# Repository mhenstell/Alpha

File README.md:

Alpha
======

Alpha is an Arduino-compatible display that includes five ultra-bright 18-segment alphanumeric displays. It's powered by USB or external supply, and can be daisy-chained. It's also internet-enabled with the inclusion of a Wifi-enabled Spark Core.

I was inspired to build the Alpha by Windell Oskay's [Alpha Clock Five](http://shop.evilmadscientist.com/productsmenu/tinykitlist/589). I loved the giant, bright LED displays, so I purchased some when I lived in China and started experimenting. The Alpha is the result of those experiments. I found that my Alpha prototypes were always sitting at my desk, powered by USB, and that I liked being able to use them for notifications or other data. I added a microcontroller with native USB (based on the Atmega32u4/Arduino Leonardo), a boost converter to run the white LEDs off of USB power, as well as the option to use a Spark Core for a wireless display.

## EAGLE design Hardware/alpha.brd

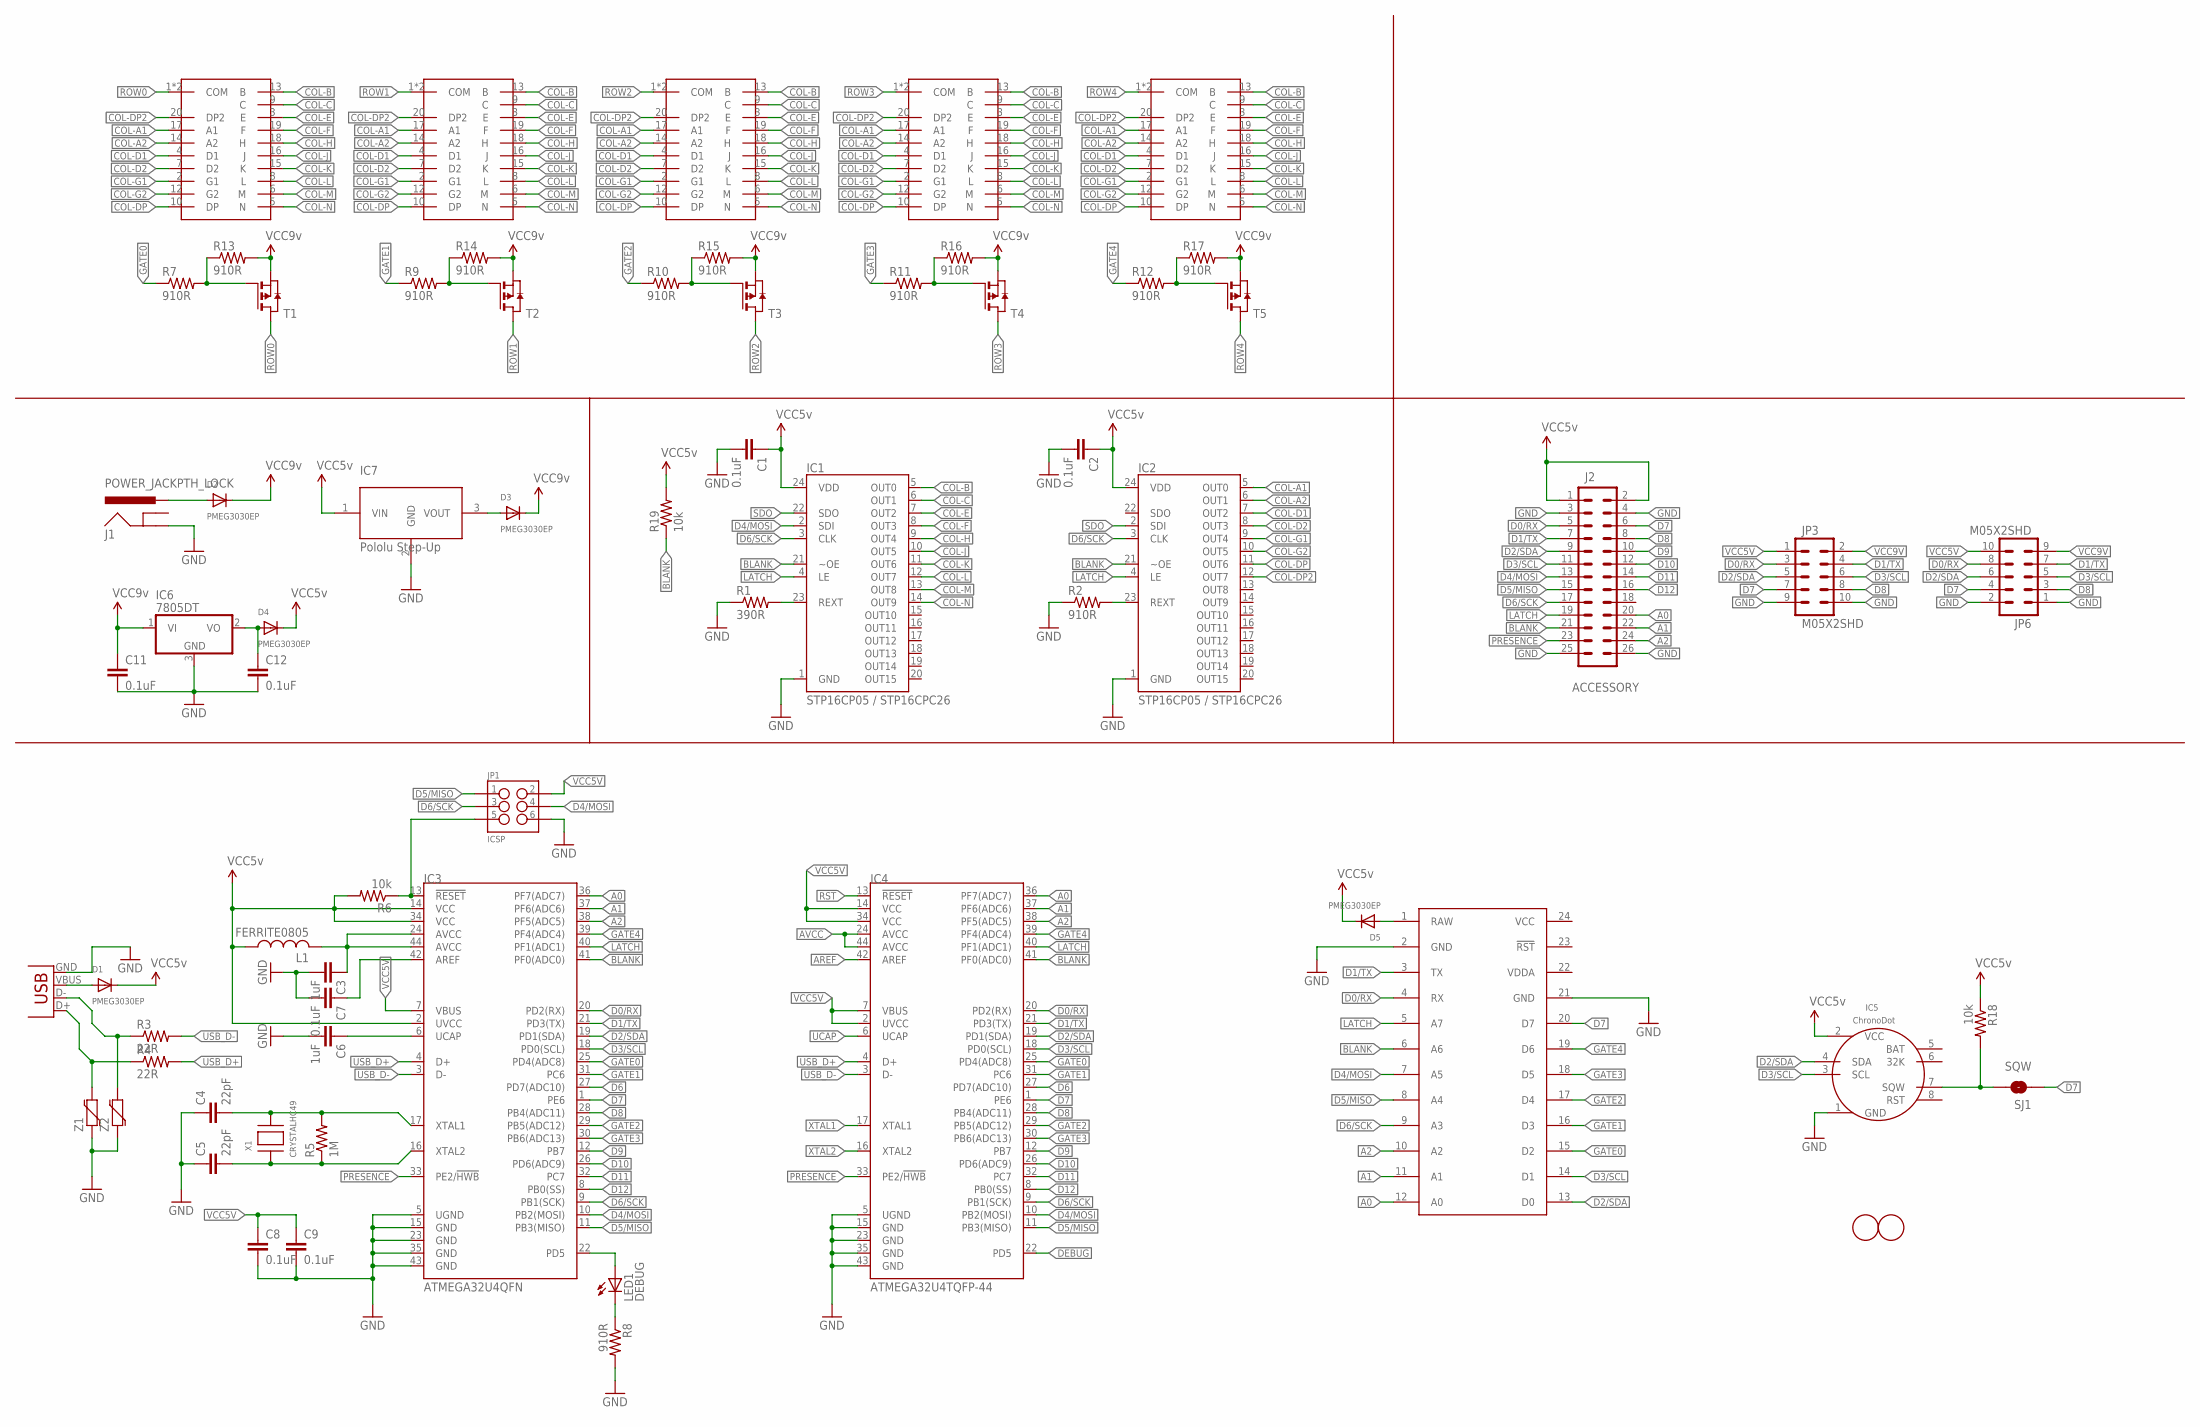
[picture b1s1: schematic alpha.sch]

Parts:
C1, C2, C7, C8, C9, C11, C12: 0.1uF; 0805; PARTNO C0805C104K5RACTU
C3, C6: 1uF; 0805; PARTNO CL21B105KBFNNNE
C4, C5: 22pF; 0805; PARTNO C0805C220J5GACTU
CORE: Spark Core; SPARK_CORE
D1, D2, D3, D4, D5: PMEG3030EP; SOD-128; PARTNO PMEG3030EP-115
IC1, IC2: STP16CP05 / STP16CPC26; SO-24DW; PARTNO STP16CPC26MTR
IC3: ATMEGA32U4QFN; QFN-44; PARTNO ATMEGA32U4-MUR
IC4: ATMEGA32U4TQFP-44; TQFP44; PARTNO ATMEGA32U4-AU
IC5: CHRONODOT
IC6: 7805DT; TO252
IC7: Pololu Step-Up; 1X03_LOCK
J1: POWER_JACKPTH_LOCK; POWER_JACK_PTH_LOCK; PARTNO PJ-202A
J2: ACCESSORY; 2X13; PARTNO SFH11-PBPC-D13-ST-BK
JP1: ICSP; 2X3-NS; PARTNO M20-9980346
JP2: USBSMD; USB-MINIB; PARTNO 690-005-299-043
JP3, JP6: M05X2SHD; 2X5-SHROUDED; PARTNO 302-S101
L1: FERRITE0805; 0805; PARTNO CIM21J601NE
LED1: DEBUG; CHIP-LED0805; PARTNO LG R971-KN-1
R1: 390R; 0805; PARTNO RC0805FR-07390RL
R2, R7, R8, R9, R10, R11, R12, R13, R14, R15, R16, R17: 910R; 0805; PARTNO MCR10ERTF9100
R3, R4: 22R; 0805; PARTNO RC0805FR-0722RL
R5: 1M; 0805; PARTNO RC0805FR-071ML
R6, R18: 10k; 0805; PARTNO RC0805JR-0710KL
R19: 10k; 0805
SEG1, SEG2, SEG3, SEG4, SEG5: BL-S230X-12
SJ1: SQW; SJ_2S-NO
T1, T2, T3, T4, T5: PMOSSOT23; SOT-23; PARTNO FDN352AP
U$1, U$2: FIDUCIAL; FIDUCIAL_1MM
X1: CRYSTALHC49; HC49; PARTNO 9C-16.000MAAJ-T
Z1, Z2: VARISTOR-0603; 0603-RES; PARTNO CG0603MLC-05E

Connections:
A0: CORE.12 (A0), IC3.36 (PF7(ADC7)), IC4.36 (PF7(ADC7)), J2.20
A1: CORE.11 (A1), IC3.37 (PF6(ADC6)), IC4.37 (PF6(ADC6)), J2.22
A2: CORE.10 (A2), IC3.38 (PF5(ADC5)), IC4.38 (PF5(ADC5)), J2.24
AREF: C7.1, IC3.42 (AREF), IC4.42 (AREF)
AVCC: C3.1, IC3.24 (AVCC), IC3.44 (AVCC), IC4.24 (AVCC), IC4.44 (AVCC), L1.2
BLANK: CORE.6 (A6), IC1.21 (~OE), IC2.21 (~OE), IC3.41 (PF0(ADC0)), IC4.41 (PF0(ADC0)), J2.21, R19.1
COL-A1: IC2.5 (OUT0), SEG1.17 (A1), SEG2.17 (A1), SEG3.17 (A1), SEG4.17 (A1), SEG5.17 (A1)
COL-A2: IC2.6 (OUT1), SEG1.14 (A2), SEG2.14 (A2), SEG3.14 (A2), SEG4.14 (A2), SEG5.14 (A2)
COL-B: IC1.5 (OUT0), SEG1.13 (B), SEG2.13 (B), SEG3.13 (B), SEG4.13 (B), SEG5.13 (B)
COL-C: IC1.6 (OUT1), SEG1.9 (C), SEG2.9 (C), SEG3.9 (C), SEG4.9 (C), SEG5.9 (C)
COL-D1: IC2.7 (OUT2), SEG1.4 (D1), SEG2.4 (D1), SEG3.4 (D1), SEG4.4 (D1), SEG5.4 (D1)
COL-D2: IC2.8 (OUT3), SEG1.7 (D2), SEG2.7 (D2), SEG3.7 (D2), SEG4.7 (D2), SEG5.7 (D2)
COL-DP: IC2.11 (OUT6), SEG1.10 (DP), SEG2.10 (DP), SEG3.10 (DP), SEG4.10 (DP), SEG5.10 (DP)
COL-DP2: IC2.12 (OUT7), SEG1.20 (DP2), SEG2.20 (DP2), SEG3.20 (DP2), SEG4.20 (DP2), SEG5.20 (DP2)
COL-E: IC1.7 (OUT2), SEG1.3 (E), SEG2.3 (E), SEG3.3 (E), SEG4.3 (E), SEG5.3 (E)
COL-F: IC1.8 (OUT3), SEG1.19 (F), SEG2.19 (F), SEG3.19 (F), SEG4.19 (F), SEG5.19 (F)
COL-G1: IC2.9 (OUT4), SEG1.2 (G1), SEG2.2 (G1), SEG3.2 (G1), SEG4.2 (G1), SEG5.2 (G1)
COL-G2: IC2.10 (OUT5), SEG1.12 (G2), SEG2.12 (G2), SEG3.12 (G2), SEG4.12 (G2), SEG5.12 (G2)
COL-H: IC1.9 (OUT4), SEG1.18 (H), SEG2.18 (H), SEG3.18 (H), SEG4.18 (H), SEG5.18 (H)
COL-J: IC1.10 (OUT5), SEG1.16 (J), SEG2.16 (J), SEG3.16 (J), SEG4.16 (J), SEG5.16 (J)
COL-K: IC1.11 (OUT6), SEG1.15 (K), SEG2.15 (K), SEG3.15 (K), SEG4.15 (K), SEG5.15 (K)
COL-L: IC1.12 (OUT7), SEG1.8 (L), SEG2.8 (L), SEG3.8 (L), SEG4.8 (L), SEG5.8 (L)
COL-M: IC1.13 (OUT8), SEG1.6 (M), SEG2.6 (M), SEG3.6 (M), SEG4.6 (M), SEG5.6 (M)
COL-N: IC1.14 (OUT9), SEG1.5 (N), SEG2.5 (N), SEG3.5 (N), SEG4.5 (N), SEG5.5 (N)
D0/RX: CORE.4 (RX), IC3.20 (PD2(RX)), IC4.20 (PD2(RX)), J2.5, JP3.3, JP6.8
D1/TX: CORE.3 (TX), IC3.21 (PD3(TX)), IC4.21 (PD3(TX)), J2.7, JP3.4, JP6.7
D2/SDA: CORE.13 (D0), IC3.19 (PD1(SDA)), IC4.19 (PD1(SDA)), IC5.4 (SDA), J2.9, JP3.5, JP6.6
D3/SCL: CORE.14 (D1), IC3.18 (PD0(SCL)), IC4.18 (PD0(SCL)), IC5.3 (SCL), J2.11, JP3.6, JP6.5
D4/MOSI: CORE.7 (A5), IC1.2 (SDI), IC3.10 (PB2(MOSI)), IC4.10 (PB2(MOSI)), J2.13, JP1.4
D5/MISO: CORE.8 (A4), IC3.11 (PB3(MISO)), IC4.11 (PB3(MISO)), J2.15, JP1.1
D6: IC3.27 (PD7(ADC10)), IC4.27 (PD7(ADC10))
D6/SCK: CORE.9 (A3), IC1.3 (CLK), IC2.3 (CLK), IC3.9 (PB1(SCK)), IC4.9 (PB1(SCK)), J2.17, JP1.3
D7: CORE.20 (D7), IC3.1 (PE6), IC4.1 (PE6), J2.6, JP3.7, JP6.4, SJ1.1
D8: IC3.28 (PB4(ADC11)), IC4.28 (PB4(ADC11)), J2.8, JP3.8, JP6.3
D9: IC3.12 (PB7), IC4.12 (PB7), J2.10
D10: IC3.26 (PD6(ADC9)), IC4.26 (PD6(ADC9)), J2.12
D11: IC3.32 (PC7), IC4.32 (PC7), J2.14
D12: IC3.8 (PB0(SS)), IC4.8 (PB0(SS)), J2.16
DEBUG: IC3.22 (PD5), IC4.22 (PD5), LED1.A
GATE0: CORE.15 (D2), IC3.25 (PD4(ADC8)), IC4.25 (PD4(ADC8)), R7.1
GATE1: CORE.16 (D3), IC3.31 (PC6), IC4.31 (PC6), R9.1
GATE2: CORE.17 (D4), IC3.29 (PB5(ADC12)), IC4.29 (PB5(ADC12)), R10.1
GATE3: CORE.18 (D5), IC3.30 (PB6(ADC13)), IC4.30 (PB6(ADC13)), R11.1
GATE4: CORE.19 (D6), IC3.39 (PF4(ADC4)), IC4.39 (PF4(ADC4)), R12.1
GND: C1.2, C2.2, C3.2, C4.1, C5.1, C6.2, C7.2, C8.2, C9.2, C11.2, C12.2, CORE.2 (GND), CORE.21 (GND), IC1.1 (GND), IC2.1 (GND), IC3.5 (UGND), IC3.15 (GND), IC3.23 (GND), IC3.35 (GND), IC3.43 (GND), IC4.5 (UGND), IC4.15 (GND), IC4.23 (GND), IC4.35 (GND), IC4.43 (GND), IC5.1 (GND), IC6.3 (GND), IC7.2 (GND), J1.GND, J2.3, J2.4, J2.25, J2.26, JP1.6, JP2.GND, JP3.9, JP3.10, JP6.1, JP6.2, R1.1, R2.1, R8.2, Z1.1, Z2.1
LATCH: CORE.5 (A7), IC1.4 (LE), IC2.4 (LE), IC3.40 (PF1(ADC1)), IC4.40 (PF1(ADC1)), J2.19
unnamed: IC1.23 (REXT), R1.2
unnamed: IC2.23 (REXT), R2.2
unnamed: D1.A, JP2.VBUS
unnamed: JP2.D-, R3.1, Z2.2
unnamed: JP2.D+, R4.1, Z1.2
unnamed: D2.A, J1.PWR
unnamed: LED1.C, R8.1
unnamed: R11.2, R16.1, T4.3 (G)
unnamed: R7.2, R13.1, T1.3 (G)
unnamed: R9.2, R14.1, T2.3 (G)
unnamed: R10.2, R15.1, T3.3 (G)
unnamed: R12.2, R17.1, T5.3 (G)
unnamed: D3.A, IC7.3 (VOUT)
unnamed: IC5.7 (SQW), R18.2, SJ1.2
unnamed: CORE.1 (RAW), D5.A
unnamed: C12.1, D4.A, IC6.2 (VO)
PRESENCE: IC3.33 (PE2/!HWB), IC4.33 (PE2/!HWB), J2.23
ROW0: SEG1.1 (COM), SEG1.11 (COM), T1.1 (D)
ROW1: SEG2.1 (COM), SEG2.11 (COM), T2.1 (D)
ROW2: SEG3.1 (COM), SEG3.11 (COM), T3.1 (D)
ROW3: SEG4.1 (COM), SEG4.11 (COM), T4.1 (D)
ROW4: SEG5.1 (COM), SEG5.11 (COM), T5.1 (D)
RST: IC3.13 (!RESET), IC4.13 (!RESET), JP1.5, R6.1
SDO: IC1.22 (SDO), IC2.2 (SDI)
UCAP: C6.1, IC3.6 (UCAP), IC4.6 (UCAP)
USB_D+: IC3.4 (D+), IC4.4 (D+), R4.2
USB_D-: IC3.3 (D-), IC4.3 (D-), R3.2
VCC5V: C1.1, C2.1, C8.1, C9.1, CORE.24 (VCC), D1.C, D4.C, D5.C, IC1.24 (VDD), IC2.24 (VDD), IC3.2 (UVCC), IC3.7 (VBUS), IC3.14 (VCC), IC3.34 (VCC), IC4.2 (UVCC), IC4.7 (VBUS), IC4.14 (VCC), IC4.34 (VCC), IC5.2 (VCC), IC7.1 (VIN), J2.1, J2.2, JP1.2, JP3.1, JP6.10, L1.1, R6.2, R18.1, R19.2
VCC9V: C11.1, D2.C, D3.C, IC6.1 (VI), JP3.2, JP6.9, R13.2, R14.2, R15.2, R16.2, R17.2, T1.2 (S), T2.2 (S), T3.2 (S), T4.2 (S), T5.2 (S)
VDDA: CORE.22 (VDDA)
XTAL1: C4.2, IC3.17 (XTAL1), IC4.17 (XTAL1), R5.2, X1.2
XTAL2: C5.2, IC3.16 (XTAL2), IC4.16 (XTAL2), R5.1, X1.1

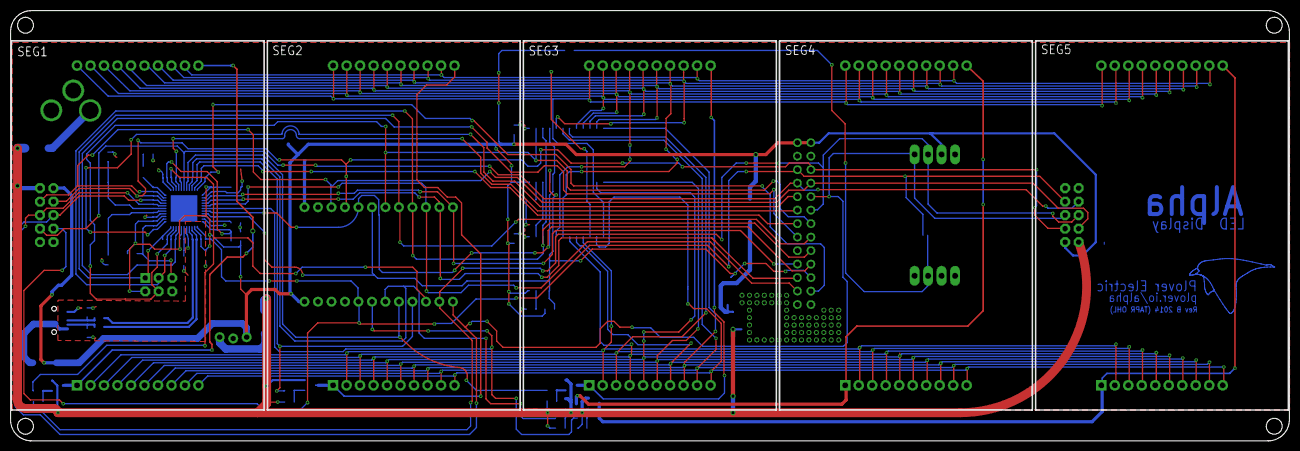
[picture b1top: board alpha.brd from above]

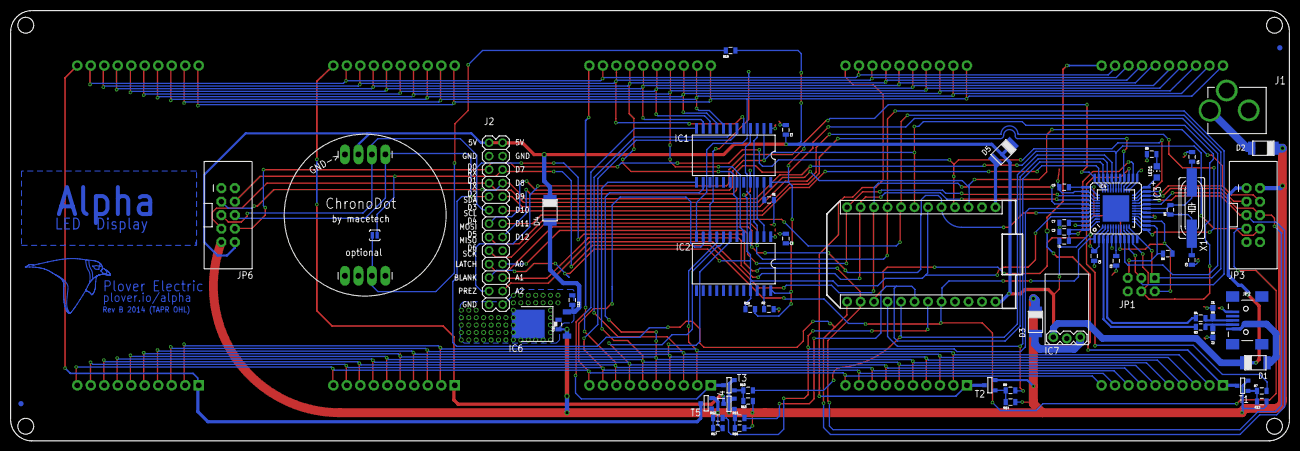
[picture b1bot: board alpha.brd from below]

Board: 2 copper layers, 240.8 x 81.0 mm, 67 parts (62 on the bottom side), 77 nets.

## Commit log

2014-06-25 init
2014-06-25 finished led part
2014-06-30 started schematic
2014-07-02 added arduinos, layout
2014-07-07 moving things around
2014-07-08 adding bigger header
2014-07-09 layout and some parts change
2014-07-09 layout
2014-07-09 more layout
2014-07-10 layout and working on silks
2014-07-12 layout, added diode
2014-07-12 added more room for screw holes and 0.1 release
2014-07-14 finished BOM
2014-07-15 changed partsdb
2014-07-17 removing partsdb
2014-08-04 sorta working
2014-08-04 grounded usb (fixes #3)
2014-08-04 increased screw hole size, added resistors, fixed mosfets (fixes #4 fixes #7 fixes #6)
2014-08-05 working pwm
2014-08-05 separated font and added OSC message receiving
2014-08-05 removed adafruit headers, added spark core, reassigning acc pins, reassigning power buses
2014-08-05 added boost converter
2014-08-06 added tssop shifter, pololu boost
2014-08-06 started rerouting
2014-08-08 layout, chronodot
2014-08-09 more routing fun
2014-08-20 rerouting to put all reflowed components closer to the center
2014-08-20 finished relayout
2014-08-20 added bird logo
2014-08-21 added 10k pullup on blank (fixes #8), moved LEDs over slightly, minor routing
2014-08-21 updating .gitignore
2014-08-21 renaming and reorganizing
2014-08-21 updating readme
2014-08-21 added Alpha text
2014-09-26 old changes from laptop, double check

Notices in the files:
parts and their libraries:
SparkFun-DigitalIC: Licensing: Creative Commons ShareAlike 4.0 International - https://creativecommons.org/licenses/by-sa/4.0
SparkFun-Passives: Licensing: CC v3.0 Share-Alike You are welcome to use this library for commercial purposes.
